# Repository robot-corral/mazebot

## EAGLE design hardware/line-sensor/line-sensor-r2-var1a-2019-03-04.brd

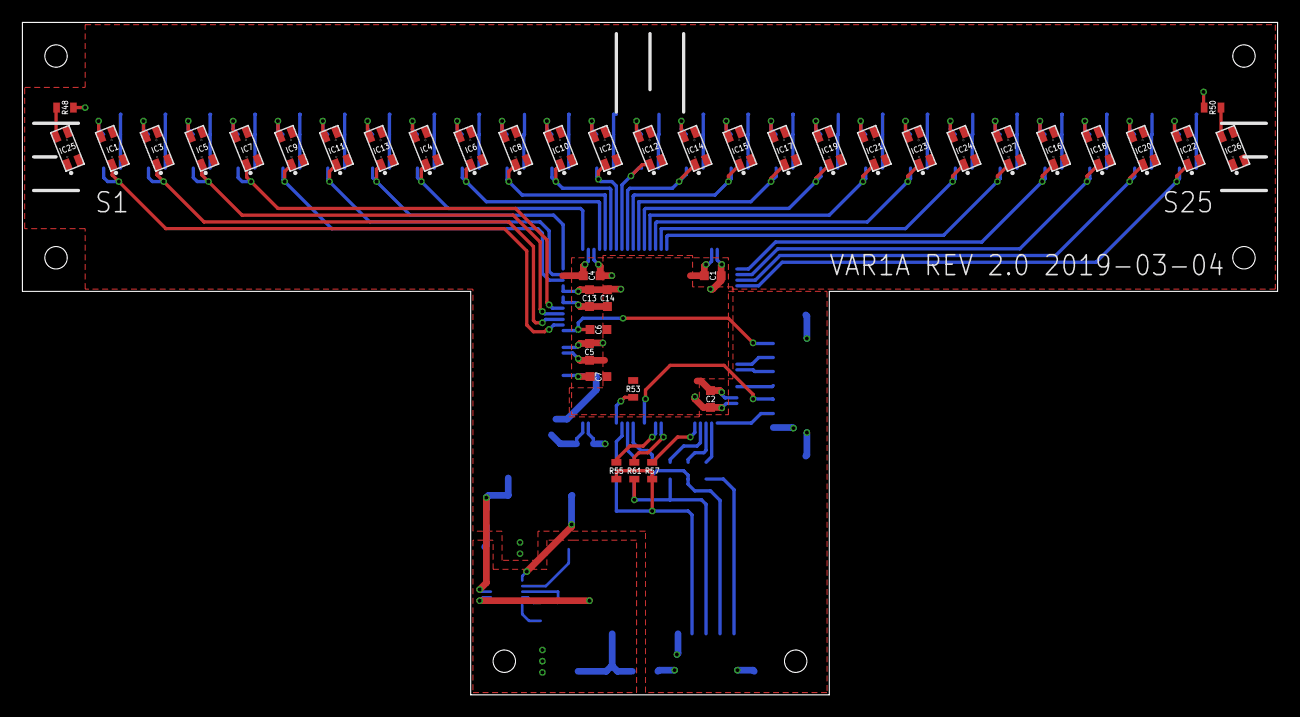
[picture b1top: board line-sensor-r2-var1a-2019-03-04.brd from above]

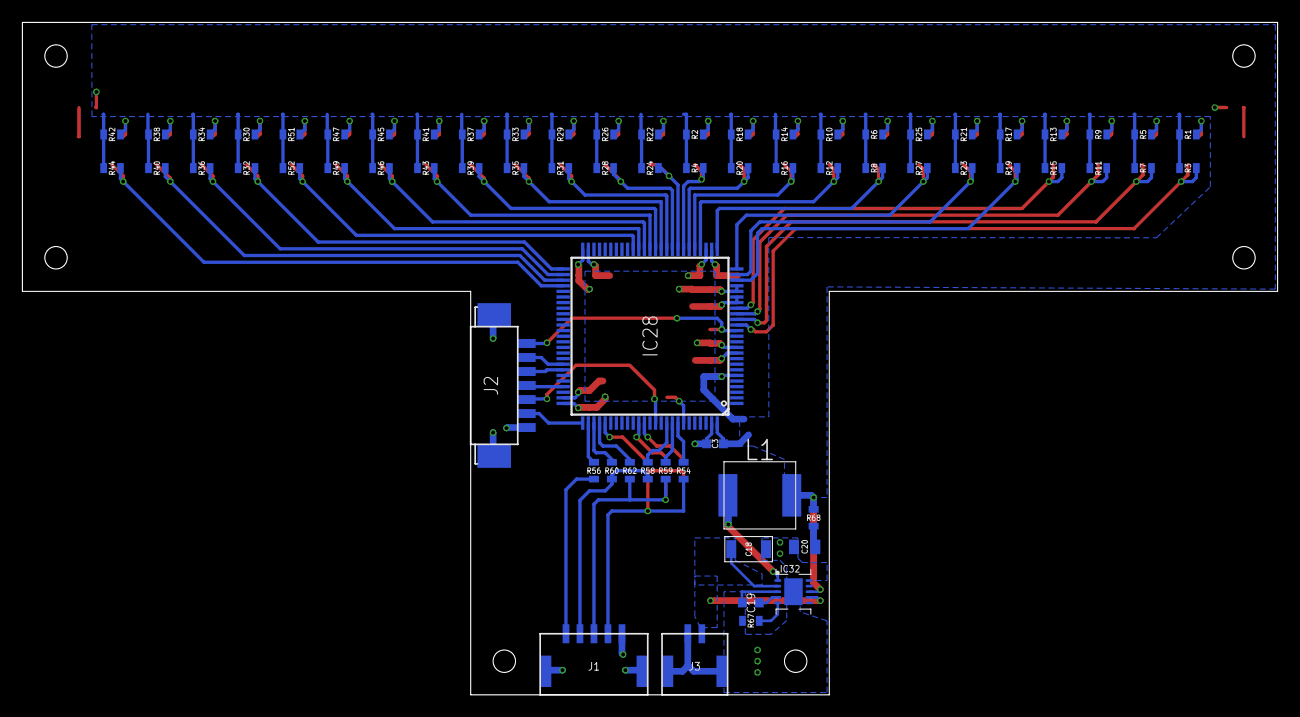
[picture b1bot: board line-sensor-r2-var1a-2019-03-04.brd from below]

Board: 2 copper layers, 112.0 x 60.0 mm, 109 parts (68 on the bottom side), 79 nets.

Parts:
C1, C2, C3, C4, C5, C6, C7, C13: 0.1u 10V X7R; CAPACITOR-0603
C14: 1u 10V X7R; CAPACITOR-0603
C18: 1u 50V X7R; CAPACITOR-1206
C19: 33n 10V X7R; CAPACITOR-0603
C20: 22u 10V X7S; CAPACITOR-0805
IC1, IC2, IC3, IC4, IC5, IC6, IC7, IC8, IC9, IC10, IC11, IC12, IC13, IC14, IC15, IC16, IC17, IC18, IC19, IC20, IC21, IC22, IC23, IC24, IC25, IC26, IC27: GP2S60
IC28: STM32L151VE; LQFP100_14X14
IC32: LM5165YDRCR; VSON-10-0.5MM
J1: MOLEX-502382-05XX
J2: MOLEX-53261-0771
J3: MOLEX-502382-02XX
L1: 150u 0.86R 0.35A; PANASONIC-SERIES-H
R1, R2, R5, R6, R9, R10, R13, R14, R17, R18, R21, R22, R25, R26, R29, R30, R33, R34, R37, R38, R41, R42, R45, R47, R48, R50, R51: 1k; RESISTOR-0603
R3, R4, R7, R8, R11, R12, R15, R16, R19, R20, R23, R24, R27, R28, R31, R32, R35, R36, R39, R40, R43, R44, R46, R49, R52: 220k; RESISTOR-0603
R53: 100k; RESISTOR-0603
R54, R55, R56, R57, R58, R59, R60, R61, R62: 0; RESISTOR-0603
R67: 121k 1%; RESISTOR-0603
R68: 0.5 5%; RESISTOR-0603

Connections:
!RST: C6.1, IC28.14, J2.1
BOOT0: IC28.94, R53.P$1
GND: C1.2, C2.2, C3.2, C4.2, C5.2, C6.2, C7.2, C13.2, C14.2, C18.P$2, C19.2, C20.2, IC1.2, IC1.3, IC2.2, IC2.3, IC3.2, IC3.3, IC4.2, IC4.3, IC5.2, IC5.3, IC6.2, IC6.3, IC7.2, IC7.3, IC8.2, IC8.3, IC9.2, IC9.3, IC10.2, IC10.3, IC11.2, IC11.3, IC12.2, IC12.3, IC13.2, IC13.3, IC14.2, IC14.3, IC15.2, IC15.3, IC16.2, IC16.3, IC17.2, IC17.3, IC18.2, IC18.3, IC19.2, IC19.3, IC20.2, IC20.3, IC21.2, IC21.3, IC22.2, IC22.3, IC23.2, IC23.3, IC24.2, IC24.3, IC25.2, IC25.3, IC26.2, IC26.3, IC27.2, IC27.3, IC28.10, IC28.19, IC28.20, IC28.27, IC28.49, IC28.74, IC28.99, IC32.3, IC32.10, IC32.PAD, J1.1, J1.G1, J1.G2, J2.7, J2.G1, J2.G2, J3.2, J3.G1, J3.G2, R53.P$2, R67.P$2
I2C1_SCL: IC28.92, R59.P$1
I2C1_SDA: IC28.93, R54.P$1
I2C1_SMBA: IC28.91, R58.P$2
IC32_SW: IC32.1, L1.1
unnamed: IC3.4, R5.P$1
unnamed: IC1.4, R1.P$1
unnamed: IC5.4, R9.P$1
unnamed: IC7.4, R13.P$1
unnamed: IC9.4, R17.P$1
unnamed: IC11.4, R21.P$1
unnamed: IC13.4, R25.P$1
unnamed: IC4.4, R6.P$1
unnamed: IC6.4, R10.P$1
unnamed: IC8.4, R14.P$1
unnamed: IC10.4, R18.P$1
unnamed: IC2.4, R2.P$1
unnamed: IC12.4, R22.P$1
unnamed: IC14.4, R26.P$1
unnamed: IC15.4, R29.P$1
unnamed: IC17.4, R33.P$1
unnamed: IC19.4, R37.P$1
unnamed: IC21.4, R41.P$1
unnamed: IC23.4, R45.P$1
unnamed: IC24.4, R47.P$1
unnamed: IC27.4, R51.P$1
unnamed: IC16.4, R30.P$1
unnamed: IC18.4, R34.P$1
unnamed: IC20.4, R38.P$1
unnamed: IC22.4, R42.P$1
unnamed: J1.2, R54.P$2, R55.P$2, R57.P$2
unnamed: J1.3, R59.P$2, R61.P$2, R62.P$2
unnamed: J1.4, R58.P$1, R60.P$1
unnamed: J1.5, R56.P$1
unnamed: IC26.4, R50.P$1
unnamed: IC25.4, R48.P$1
unnamed: IC32.5, R67.P$1
unnamed: C19.1, IC32.4
unnamed: C20.1, R68.P$2
SENSOR_1: IC1.1, IC28.15, R3.P$1
SENSOR_2: IC3.1, IC28.16, R7.P$1
SENSOR_3: IC5.1, IC28.17, R11.P$1
SENSOR_4: IC7.1, IC28.18, R15.P$1
SENSOR_5: IC9.1, IC28.23, R19.P$1
SENSOR_6: IC11.1, IC28.24, R23.P$1
SENSOR_7: IC13.1, IC28.25, R27.P$1
SENSOR_8: IC4.1, IC28.26, R8.P$1
SENSOR_9: IC6.1, IC28.29, R12.P$1
SENSOR_10: IC8.1, IC28.30, R16.P$1
SENSOR_11: IC10.1, IC28.31, R20.P$1
SENSOR_12: IC2.1, IC28.32, R4.P$1
SENSOR_13: IC12.1, IC28.33, R24.P$1
SENSOR_14: IC14.1, IC28.34, R28.P$1
SENSOR_15: IC15.1, IC28.35, R31.P$1
SENSOR_16: IC17.1, IC28.36, R35.P$1
SENSOR_17: IC19.1, IC28.37, R39.P$1
SENSOR_18: IC21.1, IC28.38, R43.P$1
SENSOR_19: IC23.1, IC28.39, R46.P$1
SENSOR_20: IC24.1, IC28.40, R49.P$1
SENSOR_21: IC27.1, IC28.41, R52.P$1
SENSOR_22: IC16.1, IC28.51, R32.P$1
SENSOR_23: IC18.1, IC28.52, R36.P$1
SENSOR_24: IC20.1, IC28.53, R40.P$1
SENSOR_25: IC22.1, IC28.54, R44.P$1
SPI3_MISO: IC28.79, R62.P$1
SPI3_MOSI: IC28.80, R57.P$1
SPI3_NSS: IC28.77, R56.P$2
SPI3_SCK: IC28.78, R60.P$2
STLINK_SWO: IC28.89, J2.5
STLINK_TCK: IC28.76, J2.6
STLINK_TMS: IC28.72, J2.4
STLINK_USART1_RX: IC28.69, J2.3
STLINK_USART1_TX: IC28.68, J2.2
USART2_RX: IC28.87, R55.P$1
USART2_TX: IC28.86, R61.P$1
VBAT: C18.P$1, IC32.2, IC32.7, J3.1
VDD: C1.1, C2.1, C3.1, C4.1, C5.1, C7.1, C13.1, C14.1, IC28.6, IC28.11, IC28.21, IC28.22, IC28.28, IC28.50, IC28.75, IC28.100, IC32.8, L1.2, R1.P$2, R2.P$2, R3.P$2, R4.P$2, R5.P$2, R6.P$2, R7.P$2, R8.P$2, R9.P$2, R10.P$2, R11.P$2, R12.P$2, R13.P$2, R14.P$2, R15.P$2, R16.P$2, R17.P$2, R18.P$2, R19.P$2, R20.P$2, R21.P$2, R22.P$2, R23.P$2, R24.P$2, R25.P$2, R26.P$2, R27.P$2, R28.P$2, R29.P$2, R30.P$2, R31.P$2, R32.P$2, R33.P$2, R34.P$2, R35.P$2, R36.P$2, R37.P$2, R38.P$2, R39.P$2, R40.P$2, R41.P$2, R42.P$2, R43.P$2, R44.P$2, R45.P$2, R46.P$2, R47.P$2, R48.P$2, R49.P$2, R50.P$2, R51.P$2, R52.P$2, R68.P$1

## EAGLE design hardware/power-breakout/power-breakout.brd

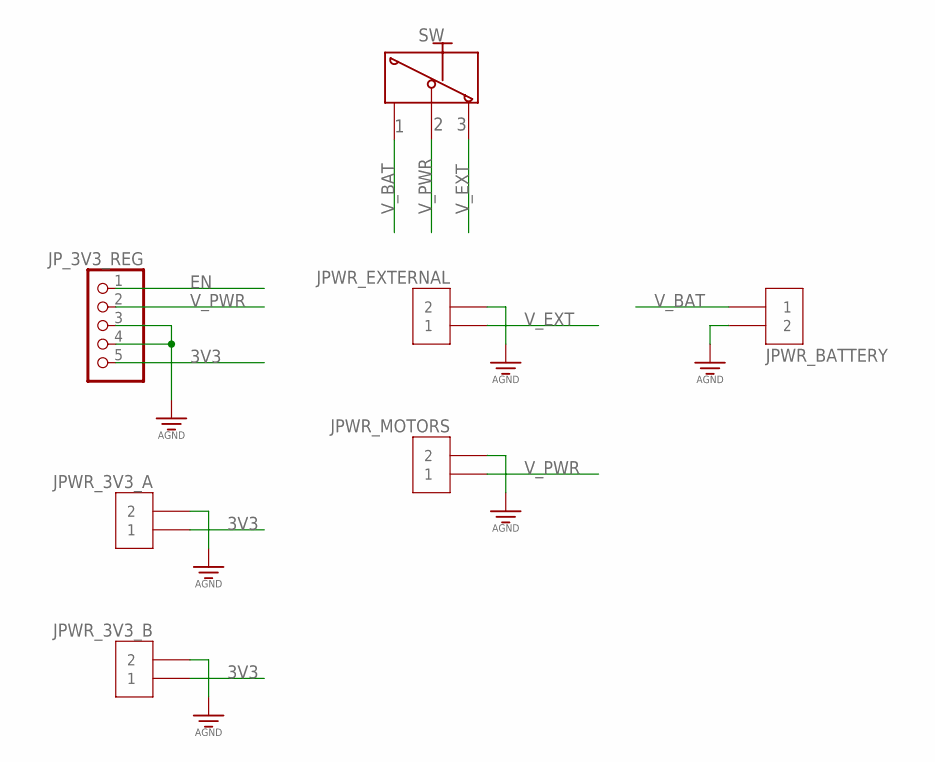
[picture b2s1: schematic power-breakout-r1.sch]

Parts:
JPWR_3V3_A, JPWR_3V3_B: WURTH_691103110002
JPWR_BATTERY: WURTH_691103110002
JPWR_EXTERNAL: JST_B2P-VH_1X2_10A; 2_PINS,0.156_PITCH
JPWR_MOTORS: WURTH_691103110002
JP_3V3_REG: CON-1X5; 1X05-CONNECTOR
SW: APEM_GH39P0

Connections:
3V3: JPWR_3V3_A.1, JPWR_3V3_B.1, JP_3V3_REG.5
AGND: JPWR_3V3_A.2, JPWR_3V3_B.2, JPWR_BATTERY.2, JPWR_EXTERNAL.2, JPWR_MOTORS.2, JP_3V3_REG.3, JP_3V3_REG.4
EN: JP_3V3_REG.1
V_BAT: JPWR_BATTERY.1, SW.P$1
V_EXT: JPWR_EXTERNAL.1, SW.P$3
V_PWR: JPWR_MOTORS.1, JP_3V3_REG.2, SW.P$2

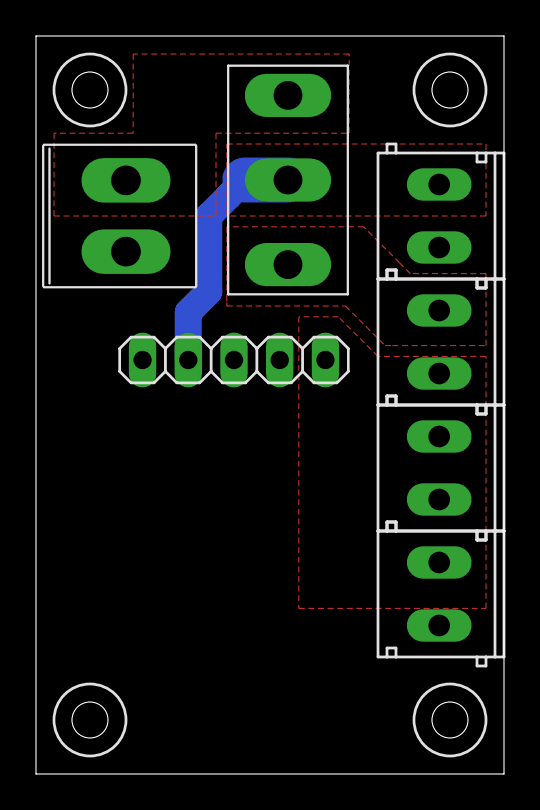
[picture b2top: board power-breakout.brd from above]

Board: 2 copper layers, 26.0 x 41.0 mm, 7 parts (0 on the bottom side), 5 nets.
